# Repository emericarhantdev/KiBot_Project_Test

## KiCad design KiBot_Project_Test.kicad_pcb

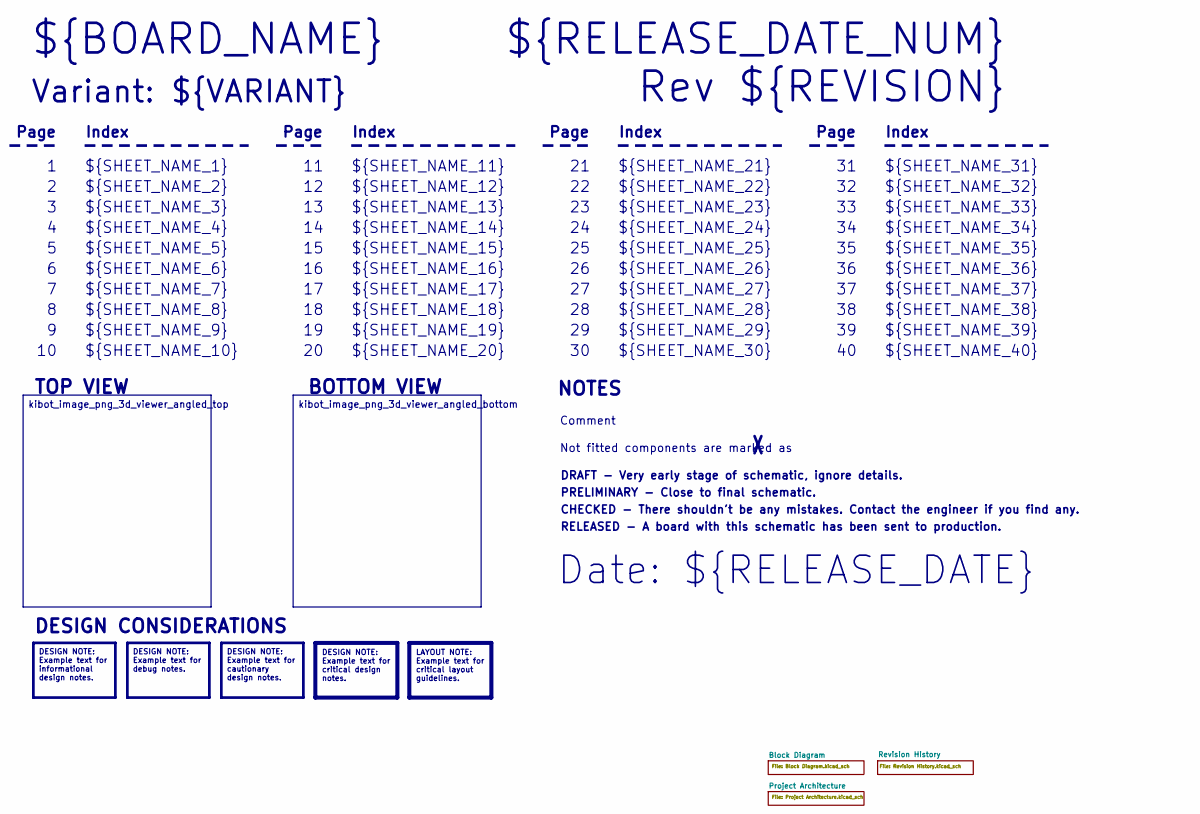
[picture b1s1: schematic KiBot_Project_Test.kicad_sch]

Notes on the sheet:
Variant: ${VARIANT}
RELEASED - A board with this schematic has been sent to production.
${SHEET_NAME_24}
Index
Page
PRELIMINARY - Close to final schematic.
${SHEET_NAME_22}
DRAFT - Very early stage of schematic, ignore details.
${SHEET_NAME_12}
${SHEET_NAME_8}
${SHEET_NAME_2}
${SHEET_NAME_5}
${SHEET_NAME_20}
${SHEET_NAME_23}
${RELEASE_DATE_NUM}
${SHEET_NAME_35}
Not fitted components are marked as
${SHEET_NAME_11}
${SHEET_NAME_6}
${SHEET_NAME_37}
${SHEET_NAME_26}
${SHEET_NAME_36}
Rev ${REVISION}
${SHEET_NAME_15}
CHECKED - There shouldn't be any mistakes. Contact the engineer if you find any.
BOTTOM VIEW
${SHEET_NAME_14}
${SHEET_NAME_21}
${SHEET_NAME_17}
${SHEET_NAME_18}
Date: ${RELEASE_DATE}
${SHEET_NAME_7}
${SHEET_NAME_31}
${BOARD_NAME}
NOTES
${SHEET_NAME_40}
${SHEET_NAME_39}
${SHEET_NAME_32}
${SHEET_NAME_1}
${SHEET_NAME_9}

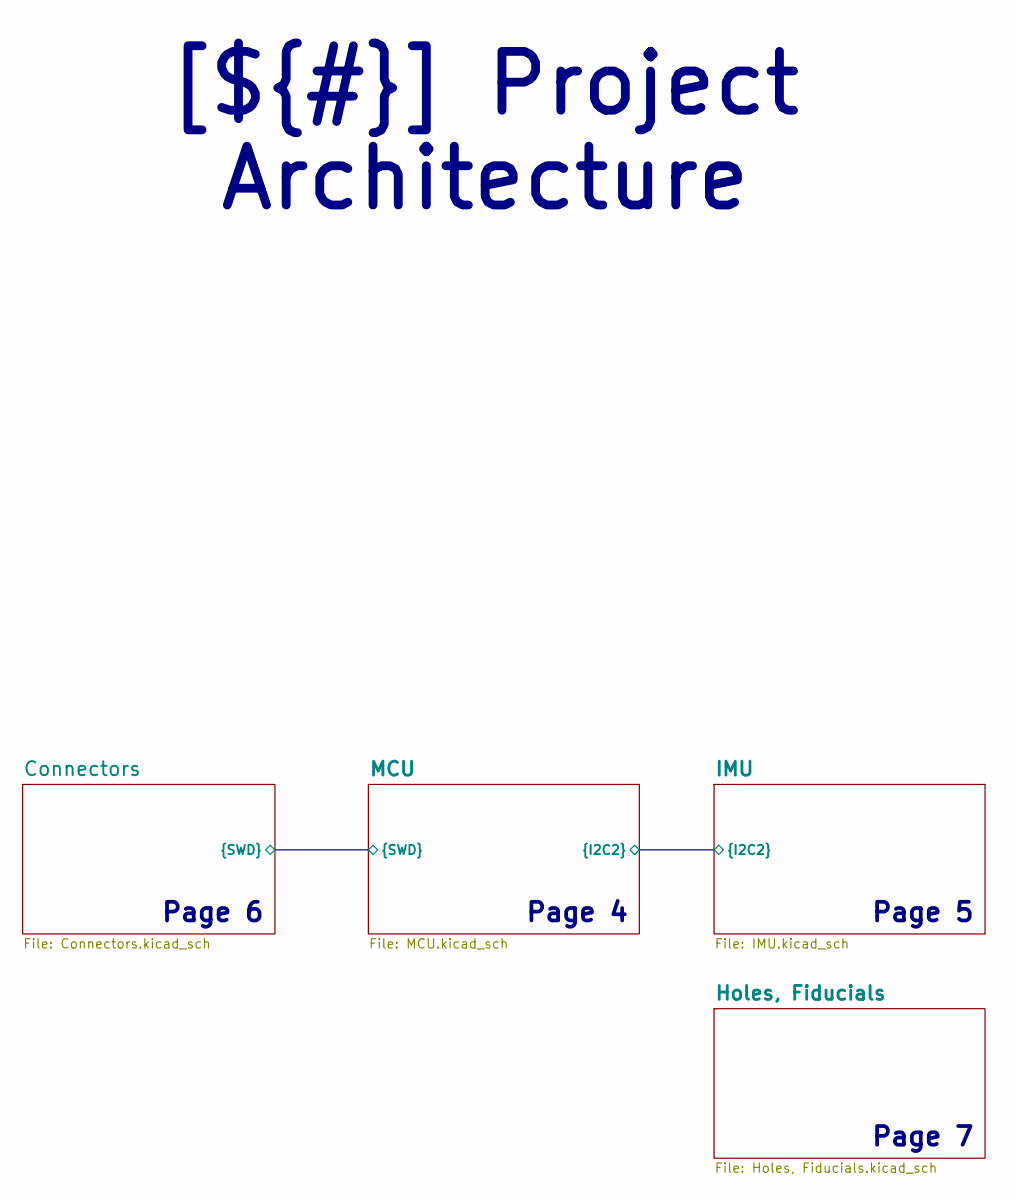
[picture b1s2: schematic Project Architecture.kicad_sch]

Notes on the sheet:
Page 6
Page 7
Page 5
Page 4
[${#}] ${TITLE}

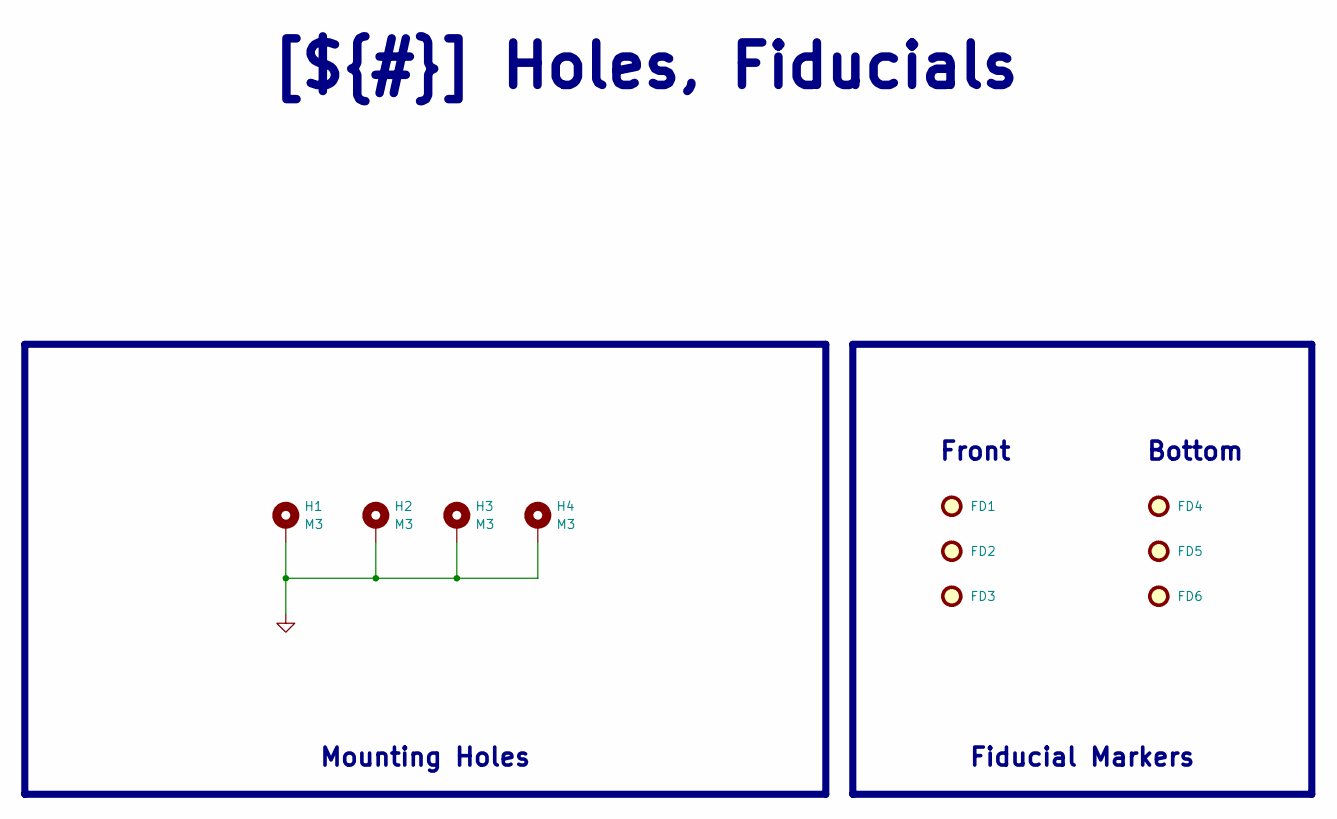
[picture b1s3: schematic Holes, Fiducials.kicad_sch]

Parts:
FD1, FD2, FD3, FD4, FD5, FD6: Fiducial; Fiducial_1mm_Mask2mm
H1, H2, H3, H4: M3; MountingHole_3.2mm_M3_Pad

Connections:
GND: H1.1 (1_1), H2.1 (1_1), H3.1 (1_1), H4.1 (1_1); also elsewhere on the board

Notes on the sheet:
[${#}] ${TITLE}
Front
Bottom
Mounting Holes
Fiducial Markers

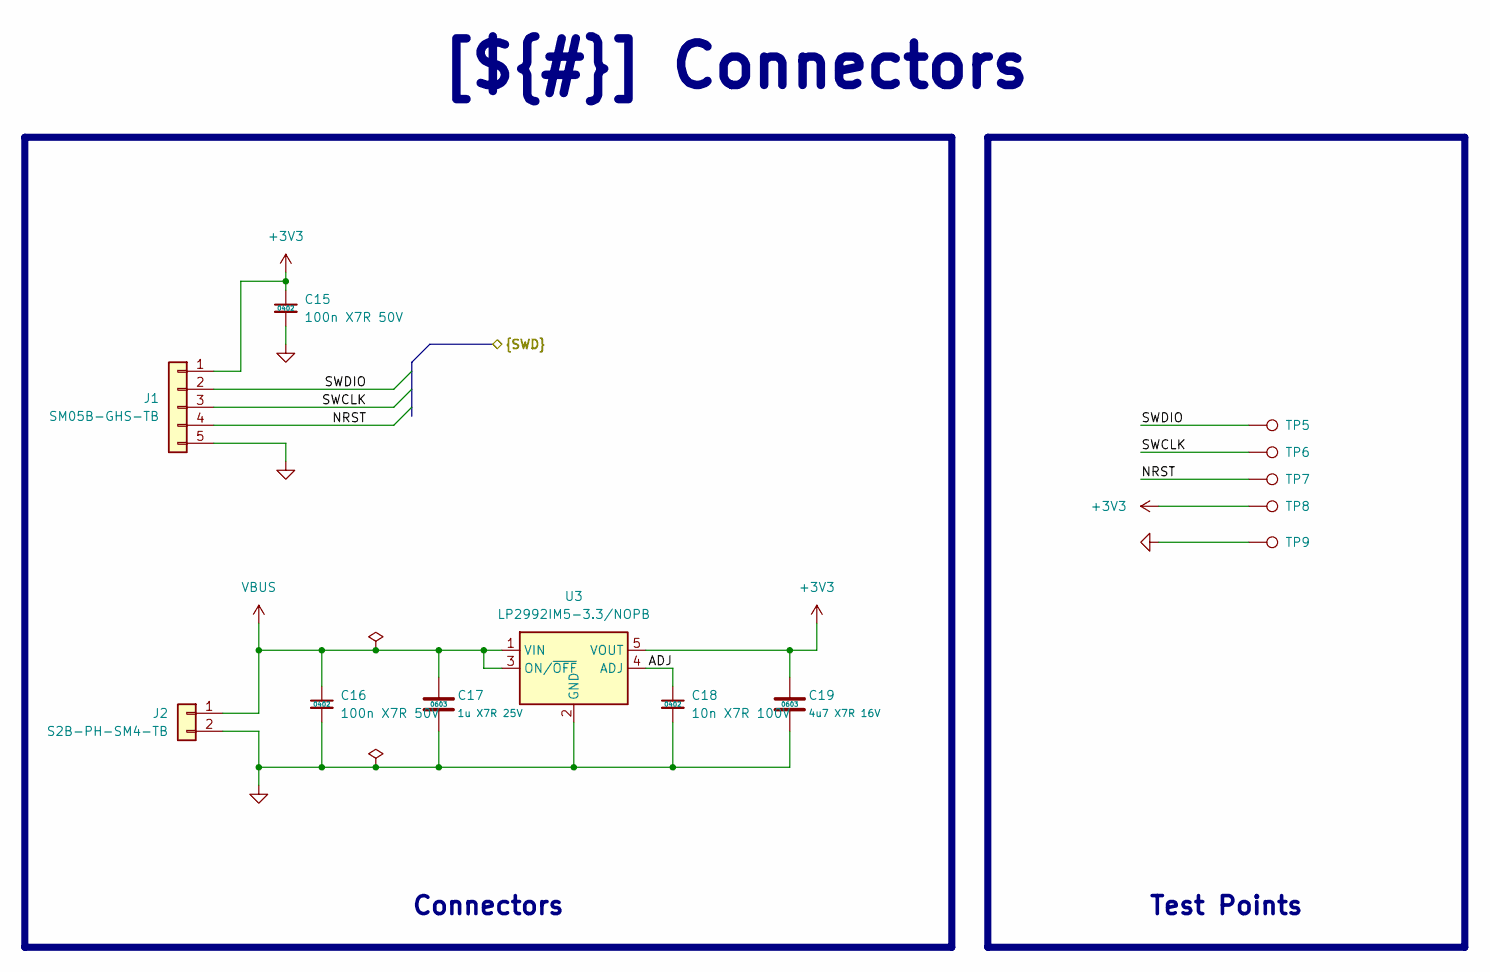
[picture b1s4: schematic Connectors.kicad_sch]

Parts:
C15, C16: 100n X7R 50V; C_0402_1005_DensityHigh; Manufacturer Part Number GCM155R71H104KE02J
C17: 1u X7R 25V; C_0603_1608_DensityHigh; Manufacturer Part Number TMK107AB7105KAHT
C18: 10n X7R 100V; C_0402_1005_DensityHigh; Manufacturer Part Number HMR105B7103KV-F
C19: 4u7 X7R 16V; C_0603_1608_DensityHigh; Manufacturer Part Number GRM188Z71C475KE21J
J1: SM05B-GHS-TB; JST_GH_SM05B-GHS-TB_1x05-1MP_P1.25mm_Horizontal; Manufacturer Part Number SM05B-GHS-TB
J2: S2B-PH-SM4-TB; JST_PH_S2B-PH-SM4-TB_1x02-1MP_P2.00mm_Horizontal; Manufacturer Part Number S2B-PH-SM4-TB
TP5, TP6, TP7, TP8, TP9: TestPoint; TestPoint_Pad_D0.5mm
U3: LP2992IM5-3.3/NOPB; SOT-23-5; Manufacturer Part Number LP2992IM5-3.3/NOPB

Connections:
+3V3: C15.1, C19.1, J1.1, TP8.1 (1_1), U3.5 (VOUT); also elsewhere on the board
/Project Architecture/Connectors/ADJ: C18.1, U3.4 (ADJ)
/Project Architecture/Connectors/NRST: J1.4, TP7.1 (1_1)
/Project Architecture/Connectors/SWCLK: J1.3, TP6.1 (1_1)
/Project Architecture/Connectors/SWDIO: J1.2, TP5.1 (1_1)
GND: C15.2, C16.2, C17.2, C18.2, C19.2, J1.5, J2.2, TP9.1 (1_1), U3.2 (GND); also elsewhere on the board
VBUS: C16.1, C17.1, J2.1, U3.1 (VIN), U3.3 (ON/~OFF)

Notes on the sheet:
Connectors
[${#}] ${TITLE}
Test Points

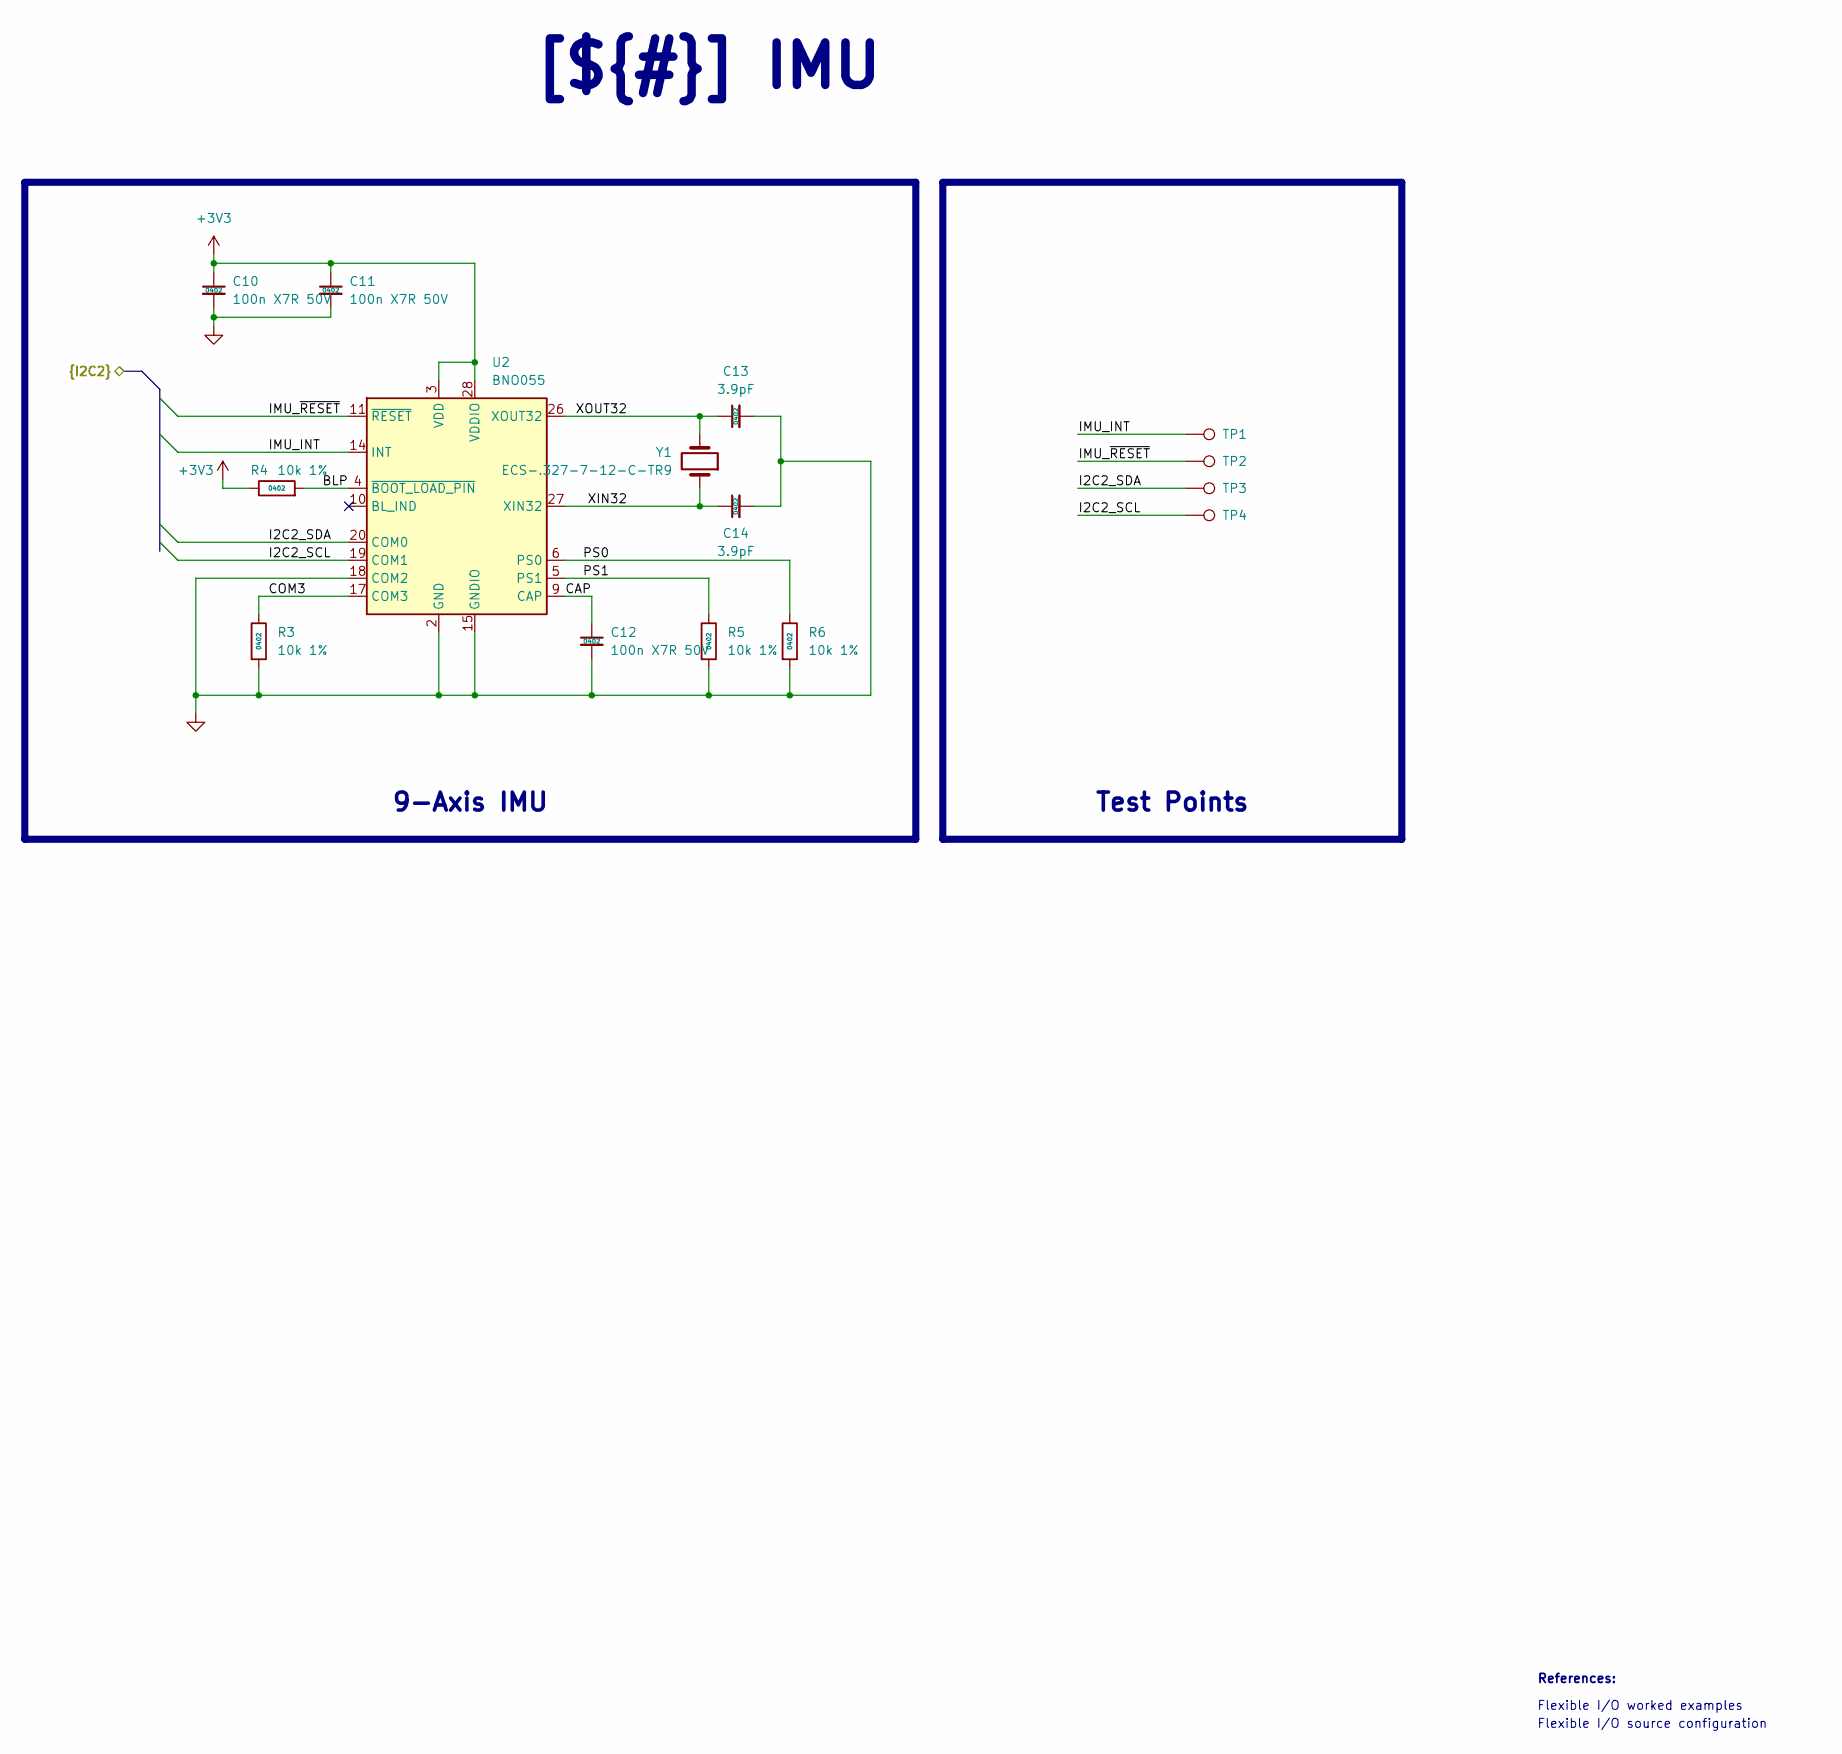
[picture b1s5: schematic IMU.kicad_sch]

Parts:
C10, C11, C12: 100n X7R 50V; C_0402_1005_DensityHigh; Manufacturer Part Number GCM155R71H104KE02J
C13, C14: 3.9pF; C_0402_1005Metric; Manufacturer Part Number 500R07S3R9BV4T
R3, R4, R5, R6: 10k 1%; R_0402_1005_DensityHigh; Manufacturer Part Number RT0402FRE0710KL
TP1, TP2, TP3, TP4: TestPoint; TestPoint_Pad_D0.5mm
U2: BNO055; LGA-28_5.2x3.8mm_P0.5mm; Manufacturer Part Number BNO055
Y1: ECS-.327-7-12-C-TR9; Crystal_SMD_2012-2Pin_2.0x1.2mm; Manufacturer Part Number ECS-.327-7-12-C-TR9

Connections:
+3V3: C10.1, C11.1, R4.1, U2.3 (VDD), U2.28 (VDDIO); also elsewhere on the board
/Project Architecture/IMU/BLP: R4.2, U2.4 (~BOOT_LOAD_PIN)
/Project Architecture/IMU/CAP: C12.1, U2.9 (CAP)
/Project Architecture/IMU/COM3: R3.1, U2.17 (COM3)
/Project Architecture/IMU/I2C2_SCL: TP4.1 (1_1), U2.19 (COM1)
/Project Architecture/IMU/I2C2_SDA: TP3.1 (1_1), U2.20 (COM0)
/Project Architecture/IMU/IMU_INT: TP1.1 (1_1), U2.14 (INT)
/Project Architecture/IMU/IMU_~RESET: TP2.1 (1_1), U2.11 (~RESET)
/Project Architecture/IMU/PS0: R6.1, U2.6 (PS0)
/Project Architecture/IMU/PS1: R5.1, U2.5 (PS1)
/Project Architecture/IMU/XIN32: C14.1, U2.27 (XIN32), Y1.1
/Project Architecture/IMU/XOUT32: C13.1, U2.26 (XOUT32), Y1.2
GND: C10.2, C11.2, C12.2, C13.2, C14.2, R3.2, R5.2, R6.2, U2.2 (GND), U2.15 (GNDIO), U2.16 (GNDIO), U2.18 (COM2), U2.25 (GNDIO); also elsewhere on the board

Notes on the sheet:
Flexible I/O worked examples
References:
Flexible I/O source configuration
[${#}] ${TITLE}
9-Axis IMU
Test Points

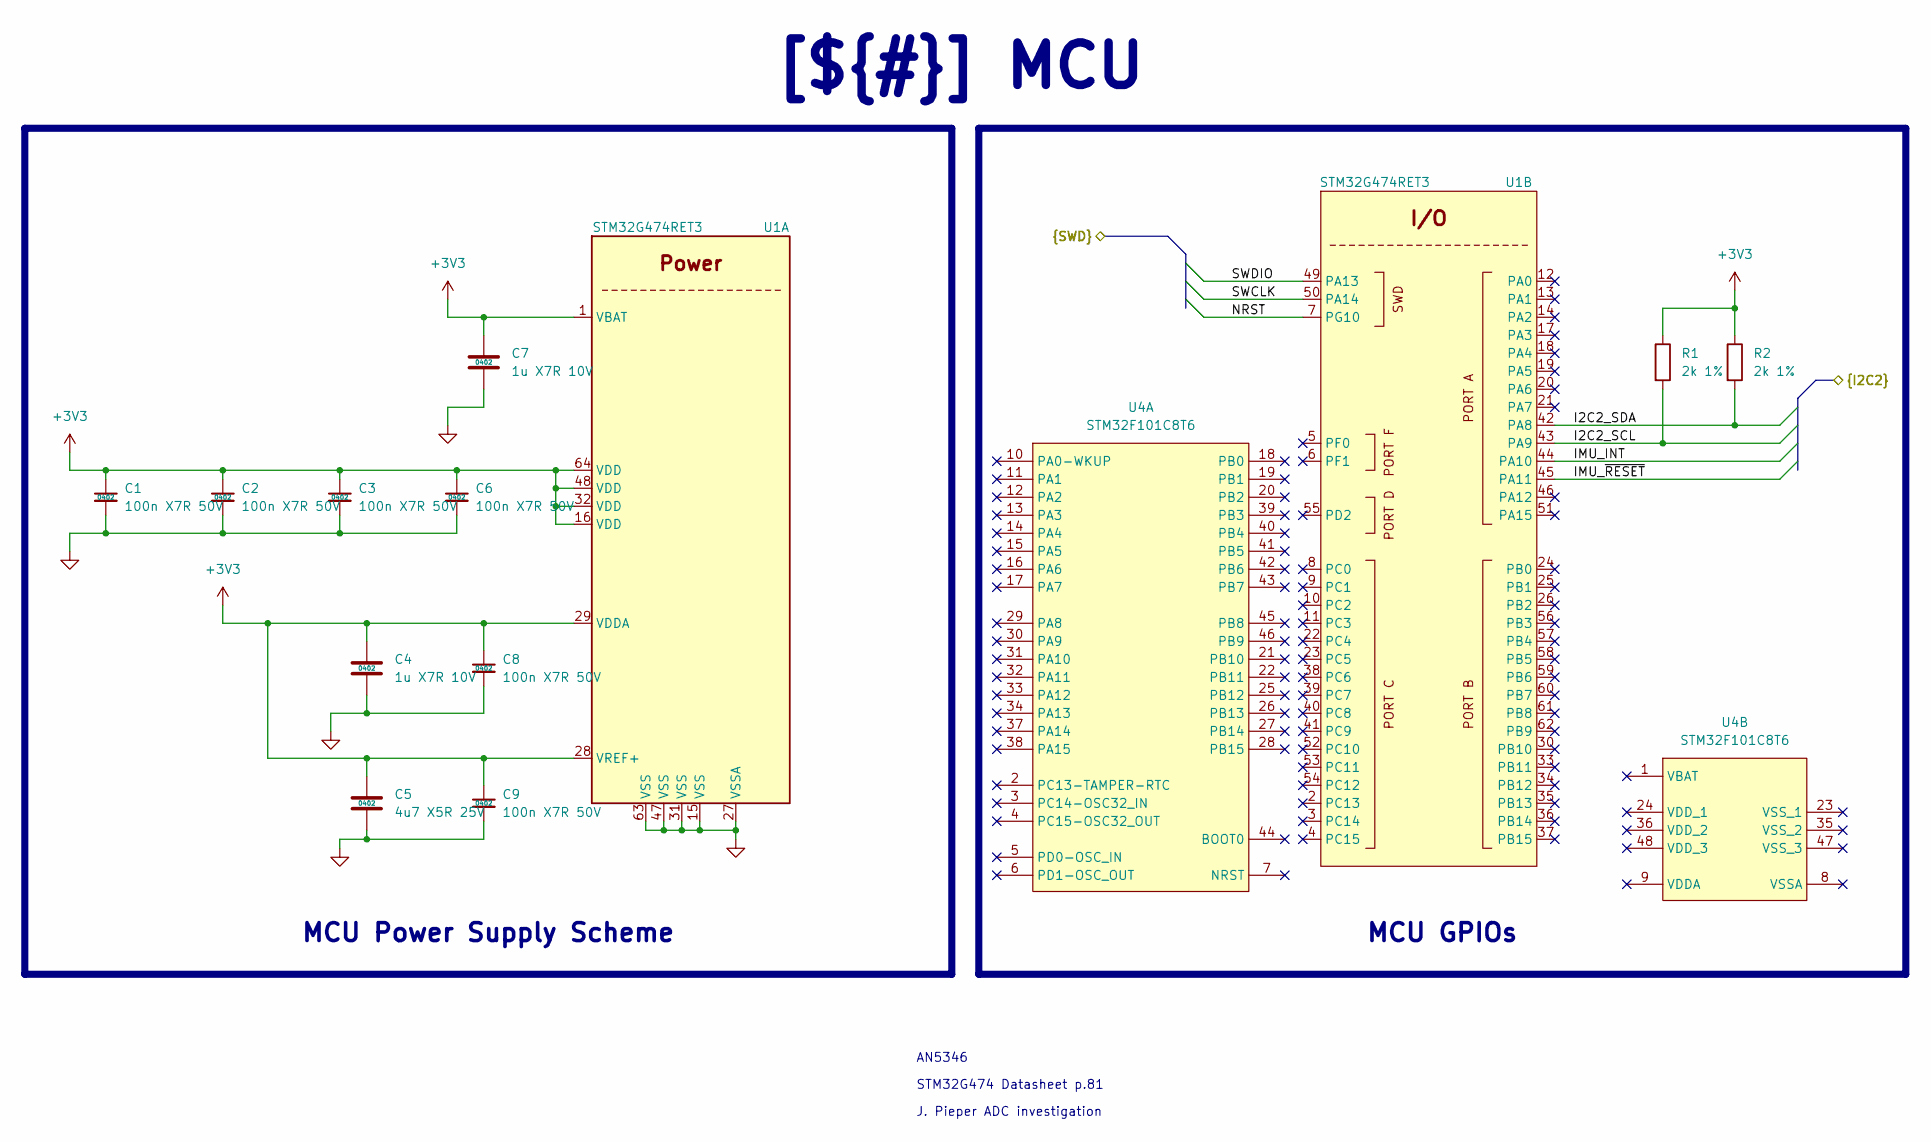
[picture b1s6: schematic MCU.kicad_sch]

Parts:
C1, C2, C3, C6, C8, C9: 100n X7R 50V; C_0402_1005_DensityHigh; Manufacturer Part Number GCM155R71H104KE02J
C4, C7: 1u X7R 10V; C_0402_1005_DensityHigh; Manufacturer Part Number GRM155Z71A105KE01J
C5: 4u7 X5R 25V; C_0402_1005_DensityHigh; Manufacturer Part Number CM05X5R475M25AH
R1, R2: 2k 1%; R_0402_1005_DensityHigh; Manufacturer Part Number ERJ-2RKF2001X
U1: STM32G474RET3; LQFP-64_10x10mm_P0.5mm; Manufacturer Part Number STM32G474RET3
U4: STM32F101C8T6; LQFP-48_7x7mm_P0.5mm; MPN STM32F101C8T6; LCSC Part C8343

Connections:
+3V3: C1.1, C2.1, C3.1, C4.1, C5.1, C6.1, C7.1, C8.1, C9.1, R1.1, R2.1, U1.1 (VBAT), U1.16 (VDD), U1.28 (VREF+), U1.29 (VDDA), U1.32 (VDD), U1.48 (VDD), U1.64 (VDD); also elsewhere on the board
/Project Architecture/MCU/I2C2_SCL: R1.2, U1.43 (PA9)
/Project Architecture/MCU/I2C2_SDA: R2.2, U1.42 (PA8)
/Project Architecture/MCU/IMU_INT: U1.44 (PA10)
/Project Architecture/MCU/IMU_~RESET: U1.45 (PA11)
/Project Architecture/MCU/NRST: U1.7 (PG10)
/Project Architecture/MCU/SWCLK: U1.50 (PA14)
/Project Architecture/MCU/SWDIO: U1.49 (PA13)
GND: C1.2, C2.2, C3.2, C4.2, C5.2, C6.2, C7.2, C8.2, C9.2, U1.15 (VSS), U1.27 (VSSA), U1.31 (VSS), U1.47 (VSS), U1.63 (VSS); also elsewhere on the board

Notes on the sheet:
J. Pieper ADC investigation
STM32G474 Datasheet p.81
AN5346
MCU GPIOs
[${#}] ${TITLE}
MCU Power Supply Scheme

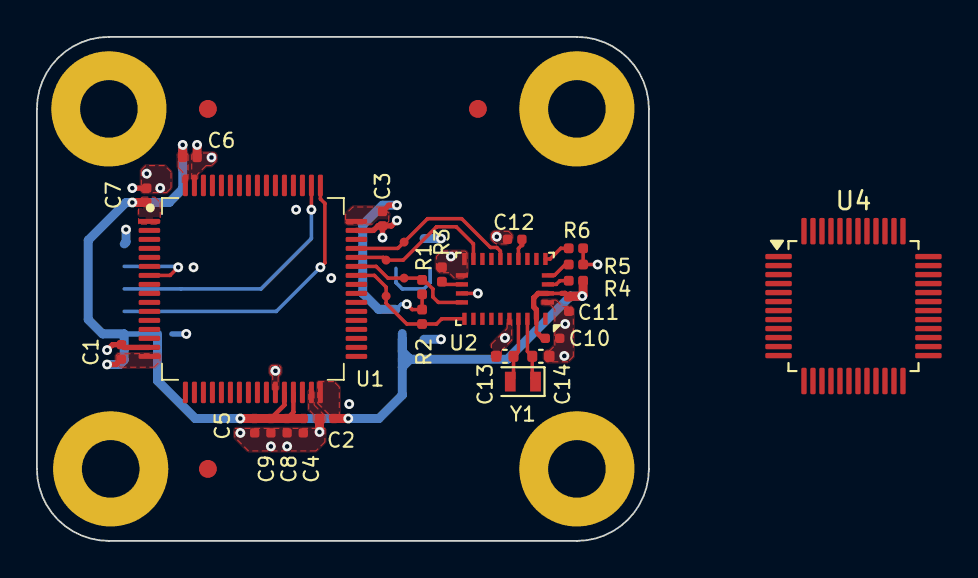
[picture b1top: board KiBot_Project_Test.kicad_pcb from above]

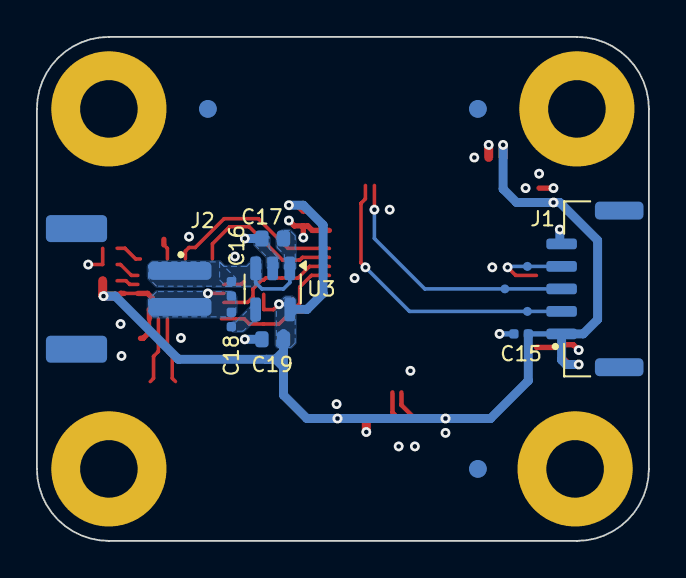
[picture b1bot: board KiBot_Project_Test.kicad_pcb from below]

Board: 4 copper layers, 34.0 x 28.0 mm, 51 parts (16 on the bottom side), 20 nets.

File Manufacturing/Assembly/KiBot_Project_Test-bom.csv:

Row,Quantity Per PCB,References,Value,Datasheet,Footprint,Description,Manufacturer,Manufacturer Part Number
1,2,C12 C13,3.9pF,https://www.johansontechnology.com/downloads/catalog/johanso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,C_0402_1005Metric,"3.9 pF ±0.1pF 50V Ceramic Capacitor C0G, NP0 0402 (1005 Metric)",Johanson Technology Inc.,500R07S3R9BV4T
2,1,C17,10n X7R 100V,https://mm.digikey.com/Volume0/opasdata/d220001/medias/docus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,C_0402_1005_DensityHigh,10000 pF ±10% 100V Ceramic Capacitor X7R 0402 (1005 Metric),Taiyo Yuden,HMR105B7103KV-F
3,11,C1 C2 C3 C6 C8 C9 C10 C11 C14 C15 C19,100n X7R 50V,https://search.murata.co.jp/Ceramy/image/img/A01X/G101/ENG/G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,C_0402_1005_DensityHigh,0.1 µF ±10% 50V Ceramic Capacitor X7R 0402 (1005 Metric),Murata Electronics,GCM155R71H104KE02J
4,1,C16,1u X7R 25V,https://mm.digikey.com/Volume0/opasdata/d220001/medias/docus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,C_0603_1608_DensityHigh,1 µF ±10% 25V Ceramic Capacitor X7R 0603 (1608 Metric),Taiyo Yuden,TMK107AB7105KAHT
5,2,C4 C7,1u X7R 10V,https://search.murata.co.jp/Ceramy/image/img/A01X/G101/ENG/G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,C_0402_1005_DensityHigh,1 µF ±10% 10V Ceramic Capacitor X7R 0402 (1005 Metric),Murata Electronics,GRM155Z71A105KE01J
6,1,C18,4u7 X7R 16V,https://search.murata.co.jp/Ceramy/image/img/A01X/G101/ENG/G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,C_0603_1608_DensityHigh,4.7 µF ±10% 16V Ceramic Capacitor X7R 0603 (1608 Metric),Murata Electronics,GRM188Z71C475KE21J
7,1,C5,4u7 X5R 25V,https://www.mouser.ch/datasheet/2/40/CM_Series_e-2835982.pdf,C_0402_1005_DensityHigh,4.7 µF ±20% 25V Ceramic Capacitor X5R 0402 (1005 Metric),KYOCERA AVX,CM05X5R475M25AH
8,1,J2,S2B-PH-SM4-TB,https://www.jst-mfg.com/product/pdf/eng/ePH.pdf,JST_PH_S2B-PH-SM4-TB_1x02-1MP_P2.00mm_Horizontal,https://www.jst-mfg.com/product/pdf/eng/ePH.pdf,JST Sales America Inc.,S2B-PH-SM4-TB
9,1,J1,SM05B-GHS-TB,https://www.jst-mfg.com/product/pdf/eng/eGH.pdf,JST_GH_SM05B-GHS-TB_1x05-1MP_P1.25mm_Horizontal,"Connector Header Surface Mount, Right Angle 5 position 0.049"" (1.25mm)",JST Sales America Inc.,SM05B-GHS-TB
10,2,R1 R2,2k 1%,https://industrial.panasonic.com/cdbs/www-data/pdf/RDA0000/A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,R_0402_1005_DensityHigh,"2 kOhms ±1% 0.1W, 1/10W Chip Resistor 0402 (1005 Metric) Automotive AEC-Q200 Thick Film",Vishay,ERJ-2RKF2001X
11,4,R3 R4 R5 R6,10k 1%,https://www.yageo.com/upload/media/product/app/datasheet/rch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,R_0402_1005_DensityHigh,"10 kOhms ±1% 0.063W, 1/16W Chip Resistor 0402 (1005 Metric) Thin Film",YAGEO,RT0402FRE0710KL
12,1,U3,BNO055,https://www.bosch-sensortec.com/media/boschsensortec/downloa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,LGA-28_5.2x3.8mm_P0.5mm,"Intelligent 9-axis absolute orientation sensor, LGA-28",Bosch Sensortec,BNO055
13,1,U4,LP2992IM5-3.3/NOPB,https://www.ti.com/lit/ds/symlink/lp2992.pdf,SOT-23-5,Micropower 250-mA Low-Noise Ultra-Low-Dropout Regulator,Texas Instruments,LP2992IM5-3.3/NOPB
14,1,U1,STM32G474RET3,https://www.st.com/resource/en/datasheet/stm32g474re.pdf,LQFP-64_10x10mm_P0.5mm,"STMicroelectronics Arm Cortex-M4 MCU, 512KB flash, 128KB RAM, 170 MHz, 1.71-3.6V, 58 GPIO, LQFP64",STMicroelectronics,STM32G474RET3
15,1,Y1,ECS-.327-7-12-C-TR9,https://ecsxtal.com/store/pdf/ECX_12.pdf,Crystal_SMD_2012-2Pin_2.0x1.2mm,"32.768 kHz ±10ppm Crystal 7pF 90 kOhms 2-SMD, No Lead",ECS Inc.,ECS-.327-7-12-C-TR9

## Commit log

2026-06-26 Update Outputs (release)
2026-06-26 Update Outputs
2026-06-26 KiCad10 forced transition test
